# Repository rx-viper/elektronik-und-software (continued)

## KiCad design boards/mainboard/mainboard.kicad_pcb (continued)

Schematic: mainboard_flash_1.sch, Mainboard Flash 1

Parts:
C1101: 100n; C_0603
J1101: FL1_CS; Measurement_Point_Round-SMD-Pad_Small
J1102: FL1_SCK; Measurement_Point_Round-SMD-Pad_Small
J1103: FL1_MISO; Measurement_Point_Round-SMD-Pad_Small
J1104: FL1_MOSI; Measurement_Point_Round-SMD-Pad_Small
U1101: SST26VF064B; SOIJ-8_5.3x5.3mm_Pitch1.27mm

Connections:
+3V3: C1101.1, U1101.3 (WP), U1101.7 (HOLD), U1101.8 (VDD); also elsewhere on the board
/Mainboard microcontroller/Flash1_CS: J1101.1, U1101.1 (CE); also elsewhere on the board
/Mainboard microcontroller/Mainboard_Flash_1/MISO: J1103.1, U1101.2 (SO); also elsewhere on the board
/Mainboard microcontroller/Mainboard_Flash_1/MOSI: J1104.1, U1101.5 (SI); also elsewhere on the board
/Mainboard microcontroller/Mainboard_Flash_1/SCK: J1102.1, U1101.6 (SCK); also elsewhere on the board
GND: C1101.2, U1101.4 (Vss); also elsewhere on the board

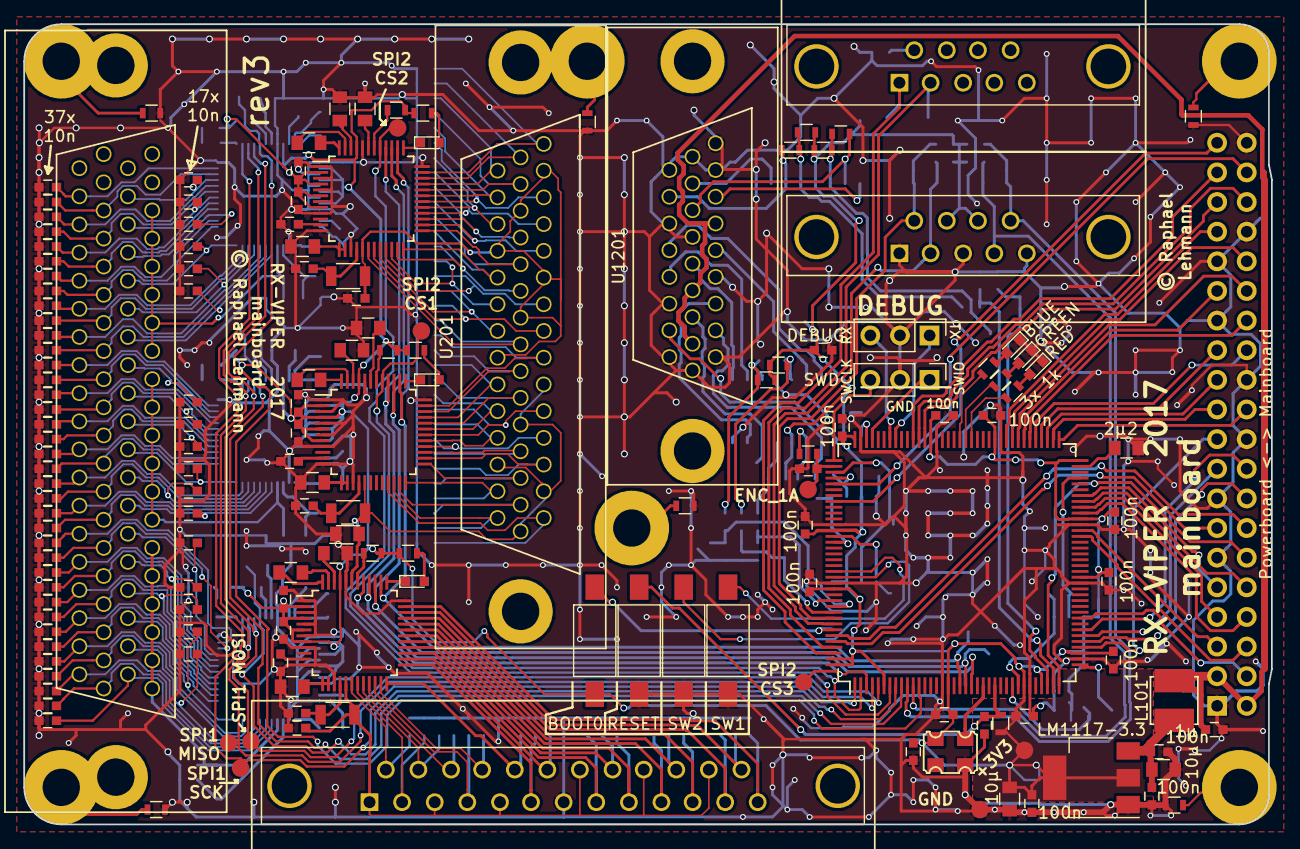
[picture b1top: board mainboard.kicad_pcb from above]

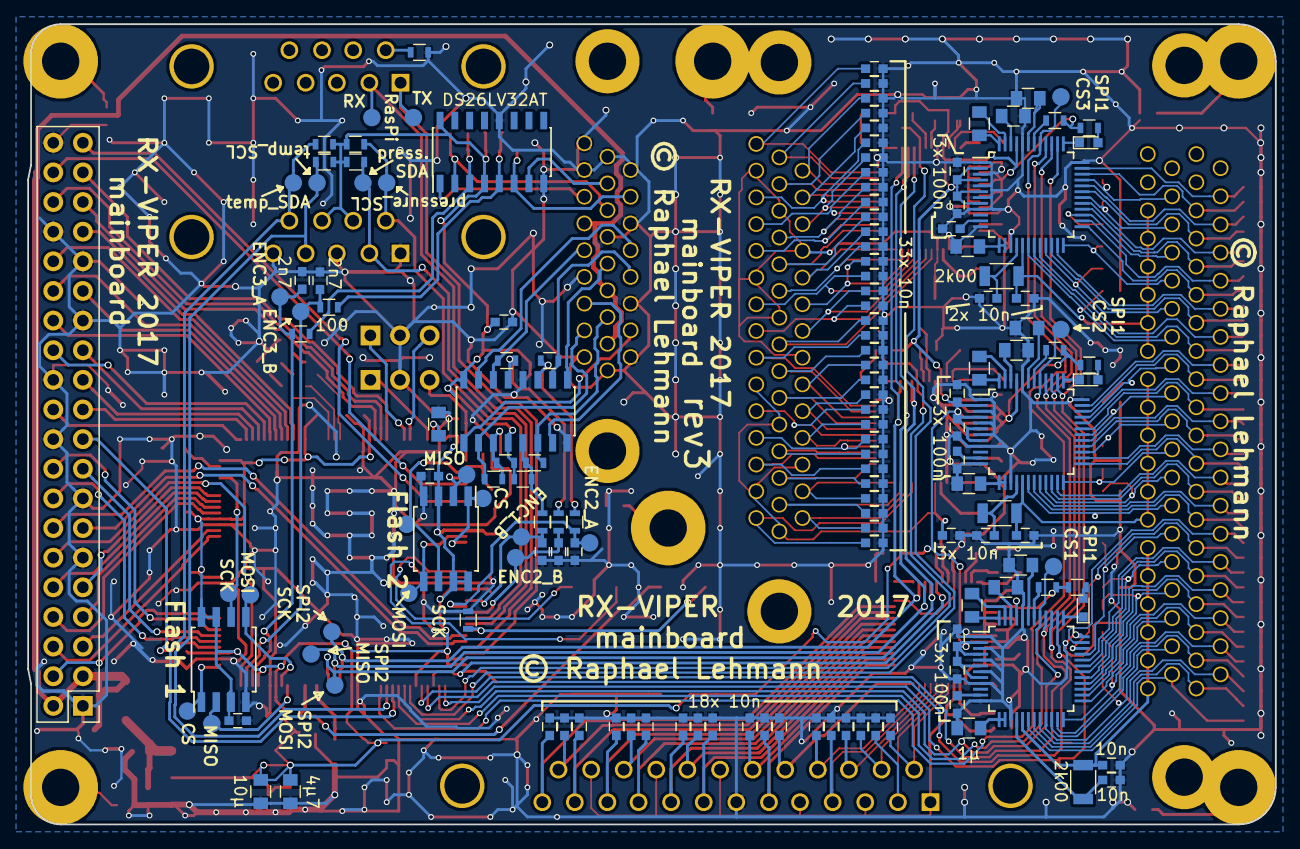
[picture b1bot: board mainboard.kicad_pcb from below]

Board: 2 copper layers, 106.9 x 68.6 mm, 319 parts (152 on the bottom side), 278 nets.

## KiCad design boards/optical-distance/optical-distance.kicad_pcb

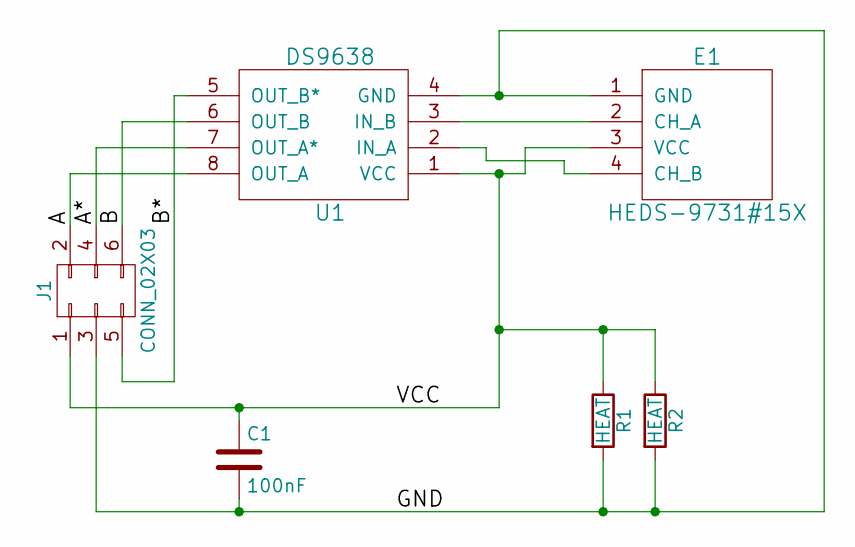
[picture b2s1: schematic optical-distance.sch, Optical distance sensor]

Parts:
C1: 100nF; C_0603_HandSoldering
E1: HEDS-9731#15X; HEDS-9731#X50
J1: CONN_02X03; Pin_Header_Straight_2x03_Pitch2.54mm
R1, R2: HEAT; R_1206
U1: DS9638; SOIC-8_3.9x4.9mm_Pitch1.27mm

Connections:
/A: J1.2, U1.8 (OUT_A)
/A*: J1.4, U1.7 (OUT_A*)
/B: J1.6, U1.6 (OUT_B)
/B*: J1.5, U1.5 (OUT_B*)
/GND: C1.2, E1.1 (GND), J1.3, R1.2, R2.2, U1.4 (GND)
/VCC: C1.1, E1.3 (VCC), J1.1, R1.1, R2.1, U1.1 (VCC)
unnamed: E1.2 (CH_A), U1.3 (IN_B)
unnamed: E1.4 (CH_B), U1.2 (IN_A)

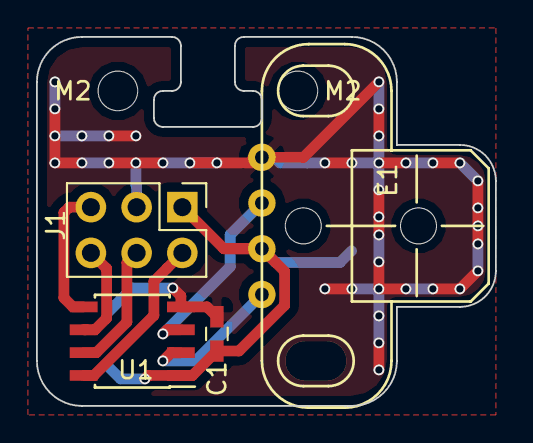
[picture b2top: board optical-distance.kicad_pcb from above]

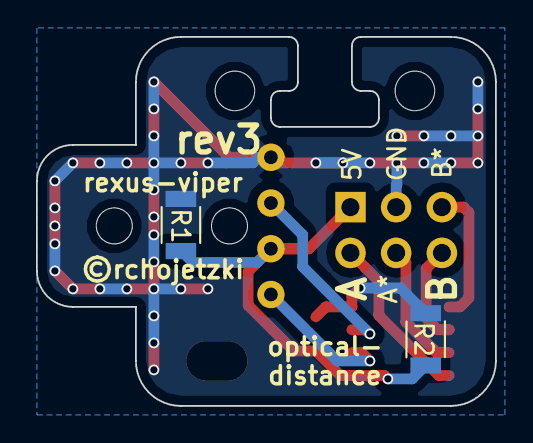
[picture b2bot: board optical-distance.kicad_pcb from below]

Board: 2 copper layers, 25.5 x 20.5 mm, 8 parts (2 on the bottom side), 8 nets.

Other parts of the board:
M2, M2#2: MountingHole_2.2mm_M2

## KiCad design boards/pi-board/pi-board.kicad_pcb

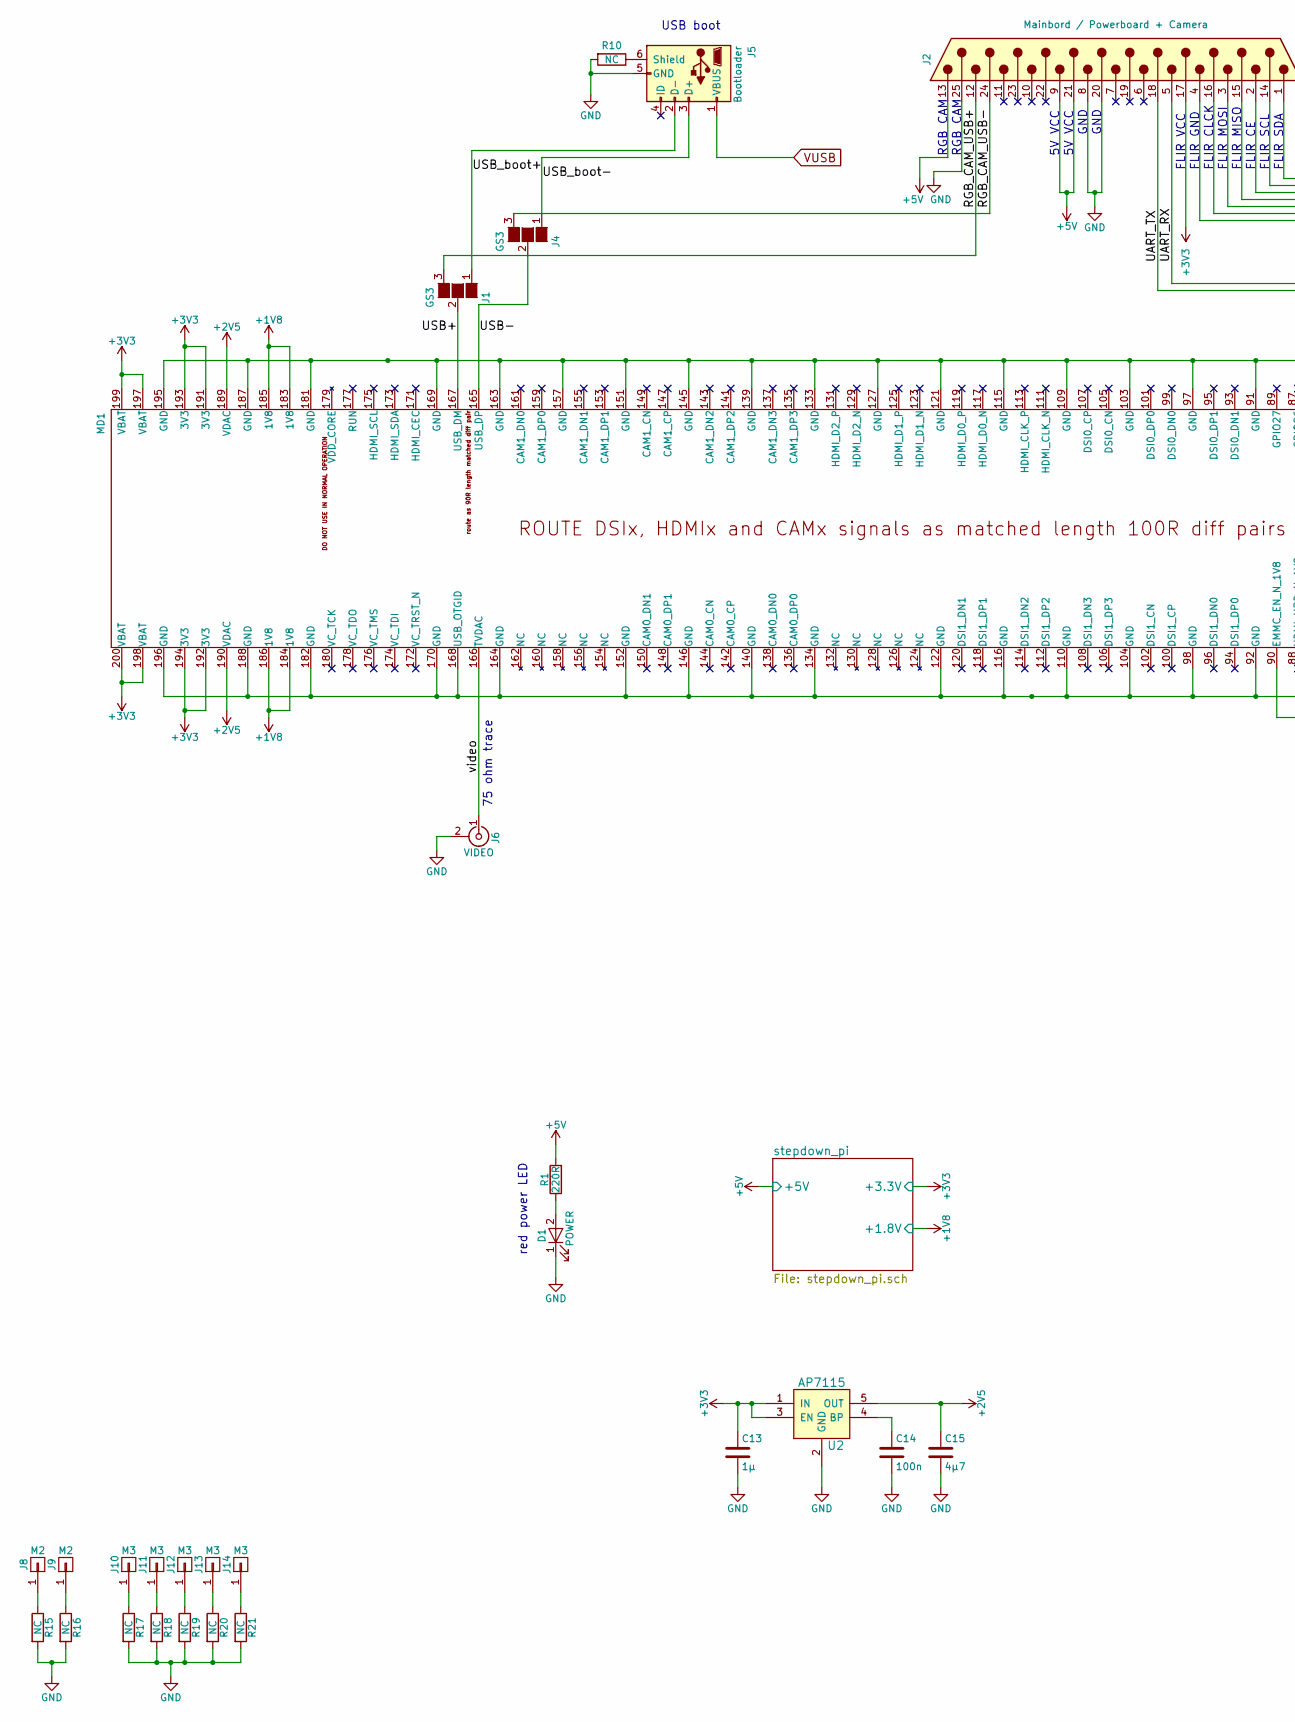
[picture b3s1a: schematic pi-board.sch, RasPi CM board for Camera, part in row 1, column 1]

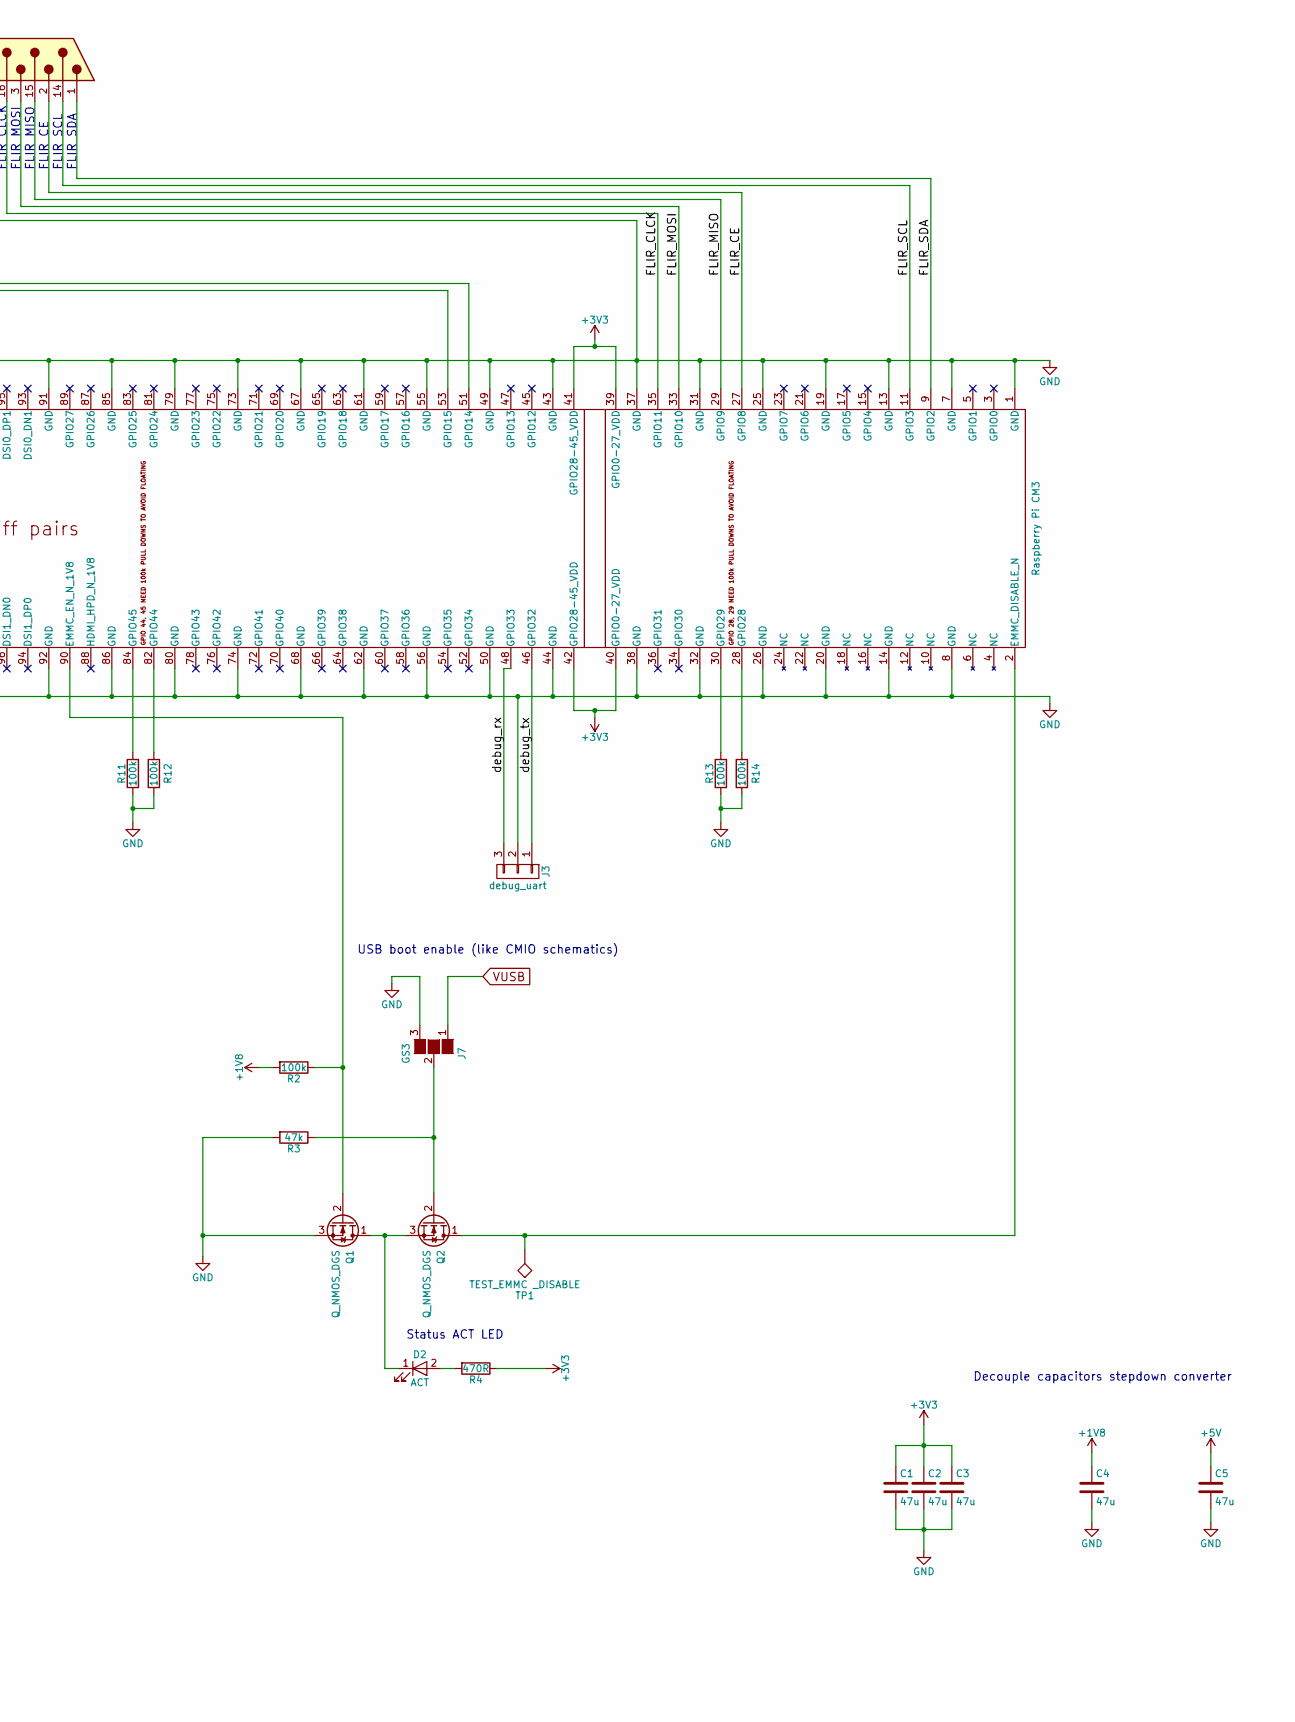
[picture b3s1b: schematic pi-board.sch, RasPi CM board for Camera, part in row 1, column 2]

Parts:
C1, C2, C3, C4, C5: 47u; C_0603_HandSoldering
C13: 1µ; C_0603
C14: 100n; C_0603
C15: 4µ7; C_0603
D1: POWER; LED_0603
D2: ACT; LED_0603
J1, J4, J7: GS3
J2: Mainbord / Powerboard + Camera; DB25MD
J3: debug_uart; Pin_Header_Straight_1x03_Pitch2.54mm
J5: Bootloader; USB_Micro-B
J6: VIDEO; BNC_Multi
J8, J9: M2; MountingHole_2.2mm_M2_Pad
J10, J11, J12, J13, J14: M3; MountingHole_3.2mm_M3_Pad
MD1: Raspberry Pi CM3; Socket_SODIMM_DDR1-2_TE_1612618_Debug
Q1, Q2: Q_NMOS_DGS; SOT-23
R1: 220R; R_0603_HandSoldering
R2, R13, R14: 100k; R_0603
R3: 47k; R_0603
R4: 470R; R_0603
R10, R15, R16, R17, R18, R19, R20, R21: NC; R_0603_HandSoldering
R11, R12: 100k; R_0603_HandSoldering
TP1: TEST_EMMC _DISABLE; Measurement_Point_Round-SMD-Pad_Small
U2: AP7115; SOT-353_SC-70-5_Handsoldering

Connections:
+1V8: C4.1, MD1.183 (1V8), MD1.184 (1V8), MD1.185 (1V8), MD1.186 (1V8), R2.2; also elsewhere on the board
+2V5: C15.1, MD1.189 (VDAC), MD1.190 (VDAC), U2.5 (OUT)
+3V3: C1.1, C2.1, C3.1, C13.1, J2.17, MD1.39 (GPIO0-27_VDD), MD1.40 (GPIO0-27_VDD), MD1.41 (GPIO28-45_VDD), MD1.42 (GPIO28-45_VDD), MD1.191 (3V3), MD1.192 (3V3), MD1.193 (3V3), MD1.194 (3V3), MD1.197 (VBAT), MD1.198 (VBAT), MD1.199 (VBAT), MD1.200 (VBAT), R4.1, U2.1 (IN), U2.3 (EN); also elsewhere on the board
+5V: C5.1, J2.9, J2.13, J2.21, R1.2; also elsewhere on the board
/FLIR_CE: J2.2, MD1.27 (GPIO8)
/FLIR_CLCK: J2.16, MD1.35 (GPIO11)
/FLIR_MISO: J2.15, MD1.29 (GPIO9)
/FLIR_MOSI: J2.3, MD1.33 (GPIO10)
/FLIR_SCL: J2.14, MD1.11 (GPIO3)
/FLIR_SDA: J2.1, MD1.9 (GPIO2)
/RGB_CAM_USB+: J1.3 (G3), J2.12
/RGB_CAM_USB-: J2.24, J4.3 (G3)
/UART_RX: J2.5, MD1.51 (GPIO14)
/UART_TX: J2.18, MD1.53 (GPIO15)
/USB+: J1.2 (G2), MD1.167 (USB_DM)
/USB-: J4.2 (G2), MD1.165 (USB_DP)
/USB_boot+: J1.1 (G1), J5.2 (D-)
/USB_boot-: J4.1 (G1), J5.3 (D+)
/debug_rx: J3.3, MD1.48 (GPIO33)
/debug_tx: J3.1, MD1.46 (GPIO32)
/video: J6.1 (In), MD1.166 (TVDAC)
GND: C1.2, C2.2, C3.2, C4.2, C5.2, C13.2, C14.2, C15.2, D1.1 (K), J2.4, J2.8, J2.20, J2.25, J3.2, J5.5 (GND), J6.2 (Ext), J7.3 (G3), MD1.1 (GND), MD1.7 (GND), MD1.8 (GND), MD1.13 (GND), MD1.14 (GND), MD1.19 (GND), MD1.20 (GND), MD1.25 (GND), MD1.26 (GND), MD1.31 (GND), MD1.32 (GND), MD1.37 (GND), MD1.38 (GND), MD1.43 (GND), MD1.44 (GND), MD1.49 (GND), MD1.50 (GND), MD1.55 (GND), MD1.56 (GND), MD1.61 (GND), MD1.62 (GND), MD1.67 (GND), MD1.68 (GND), MD1.73 (GND), MD1.74 (GND), MD1.79 (GND), MD1.80 (GND), MD1.85 (GND), MD1.86 (GND), MD1.91 (GND), MD1.92 (GND), MD1.97 (GND), MD1.98 (GND), MD1.103 (GND), MD1.104 (GND), MD1.109 (GND), MD1.110 (GND), MD1.115 (GND), MD1.116 (GND), MD1.121 (GND), MD1.122 (GND), MD1.127 (GND), MD1.133 (GND), MD1.134 (GND), MD1.139 (GND), MD1.140 (GND), MD1.145 (GND), MD1.146 (GND), MD1.151 (GND), MD1.152 (GND), MD1.157 (GND), MD1.163 (GND), MD1.164 (GND), MD1.168 (USB_OTGID), MD1.169 (GND), MD1.170 (GND), MD1.181 (GND), MD1.182 (GND), MD1.187 (GND), MD1.188 (GND), MD1.195 (GND), MD1.196 (GND), Q1.3 (S), R3.2, R10.2, R11.1, R12.1, R13.1, R14.1, R15.2, R16.2, R17.2, R18.2, R19.2, R20.2, R21.2, U2.2 (GND); also elsewhere on the board
unnamed: C14.1, U2.4 (BP)
unnamed: D1.2 (A), R1.1
unnamed: D2.1 (K), Q1.1 (D), Q2.3 (S)
unnamed: D2.2 (A), R4.2
unnamed: J5.6 (Shield), R10.1
unnamed: J7.2 (G2), Q2.2 (G), R3.1
unnamed: J8.1, R15.1
unnamed: J9.1, R16.1
unnamed: J10.1, R17.1
unnamed: J11.1, R18.1
unnamed: J12.1, R19.1
unnamed: J13.1, R20.1
unnamed: J14.1, R21.1
unnamed: MD1.2 (EMMC_DISABLE_N), Q2.1 (D), TP1.1
unnamed: MD1.28 (GPIO28), R14.2
unnamed: MD1.30 (GPIO29), R13.2
unnamed: MD1.82 (GPIO44), R12.2
unnamed: MD1.84 (GPIO45), R11.2
unnamed: MD1.90 (EMMC_EN_N_1V8), Q1.2 (G), R2.1
VUSB: J5.1 (VBUS), J7.1 (G1)

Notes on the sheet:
red power LED
Status ACT LED
USB boot enable (like CMIO schematics)
USB boot
RGB CAM
FLIR VCC
FLIR GND
FLIR CLCK
FLIR MOSI
FLIR MISO
FLIR CE
FLIR SCL
FLIR SDA
5V VCC
GND
Decouple capacitors stepdown converter
75 ohm trace

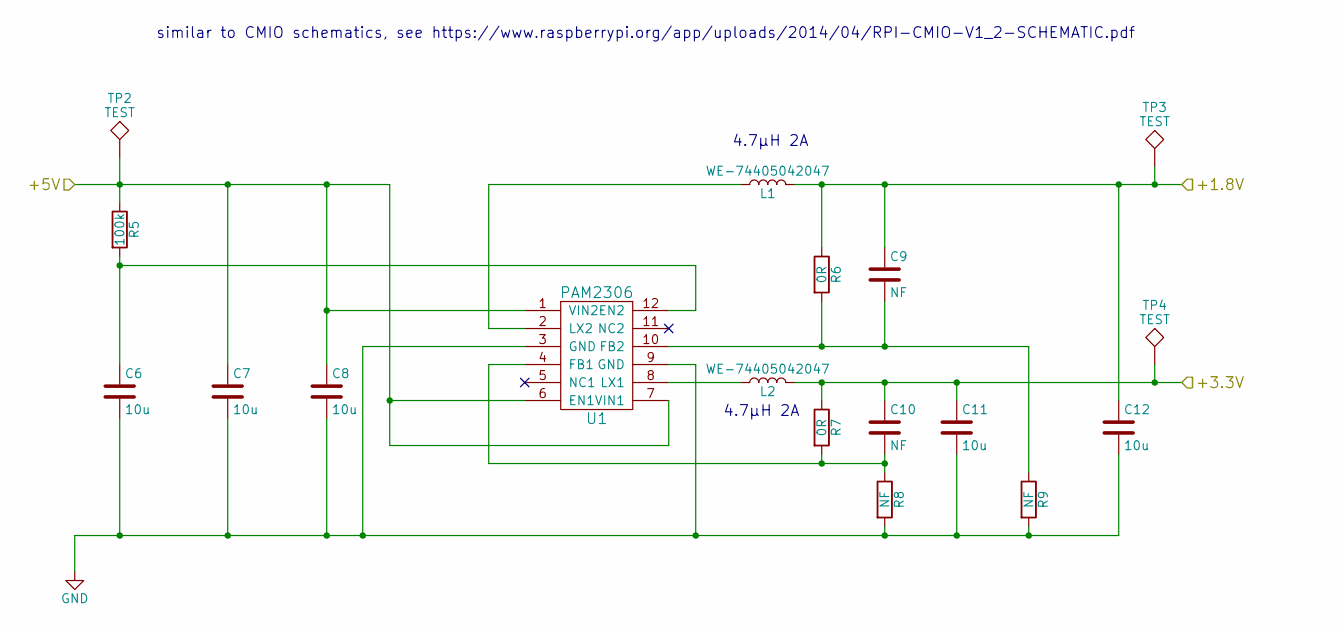
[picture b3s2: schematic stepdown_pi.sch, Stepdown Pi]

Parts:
C6, C8: 10u; C_0603
C7, C11, C12: 10u; C_0603_HandSoldering
C9, C10: NF; C_0603_HandSoldering
L1, L2: WE-74405042047; Inductor_Taiyo-Yuden_NR-50xx_HandSoldering
R5: 100k; R_0603
R6, R7: 0R; R_0603_HandSoldering
R8: NF; R_0603_HandSoldering
R9: NF; R_0603
TP2, TP3, TP4: TEST; Measurement_Point_Round-SMD-Pad_Small
U1: PAM2306; pam2306

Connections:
+1V8: C9.1, C12.1, L1.2, R6.1, TP3.1; also elsewhere on the board
+3V3: C10.1, C11.1, L2.2, R7.1, TP4.1; also elsewhere on the board
+5V: C7.1, C8.1, R5.1, TP2.1, U1.1 (VIN2), U1.6 (EN1), U1.7 (VIN1); also elsewhere on the board
GND: C6.2, C7.2, C8.2, C11.2, C12.2, R8.2, R9.2, U1.3 (GND), U1.9 (GND); also elsewhere on the board
unnamed: C6.1, R5.2, U1.12 (EN2)
unnamed: C9.2, R6.2, R9.1, U1.10 (FB2)
unnamed: C10.2, R7.2, R8.1, U1.4 (FB1)
unnamed: L1.1, U1.2 (LX2)
unnamed: L2.1, U1.8 (LX1)

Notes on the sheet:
similar to CMIO schematics, see https://www.raspberrypi.org/app/uploads/2014/04/RPI-CMIO-V1_2-SCHEMATIC.pdf
4.7µH 2A

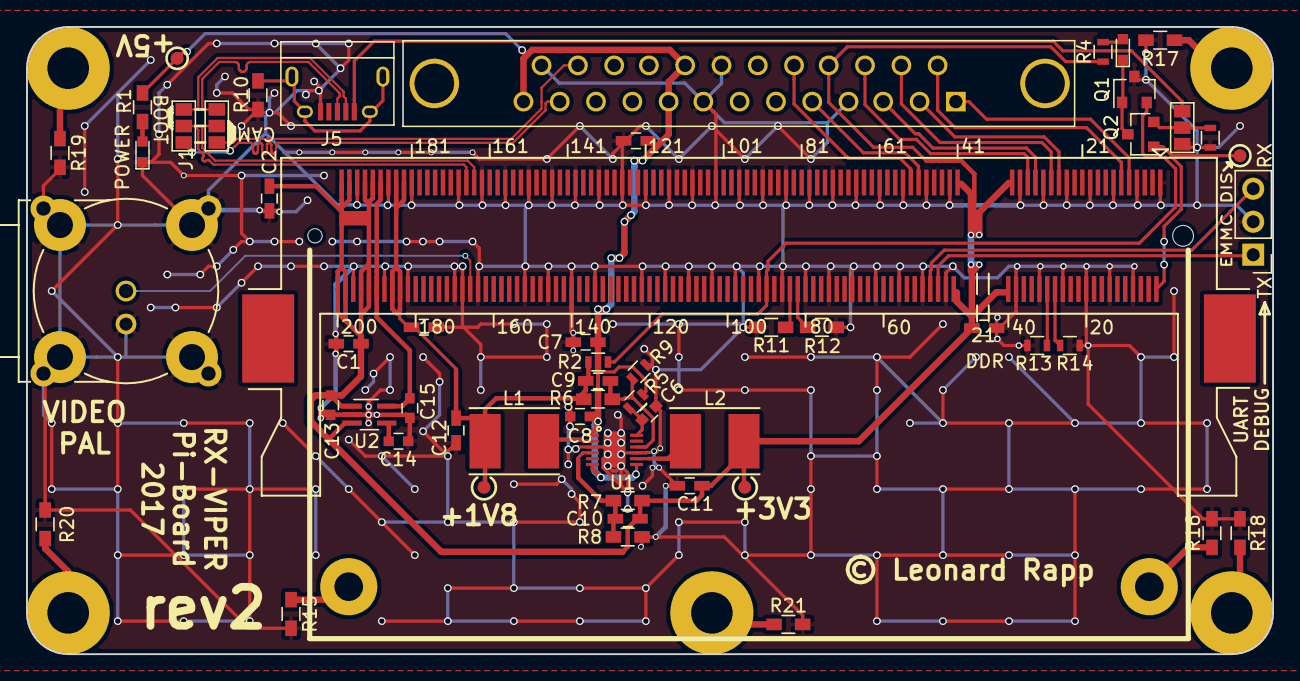
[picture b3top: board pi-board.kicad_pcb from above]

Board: 2 copper layers, 95.9 x 48.3 mm, 63 parts (0 on the bottom side), 47 nets.

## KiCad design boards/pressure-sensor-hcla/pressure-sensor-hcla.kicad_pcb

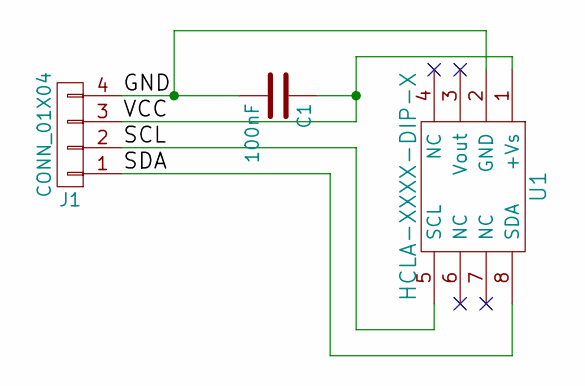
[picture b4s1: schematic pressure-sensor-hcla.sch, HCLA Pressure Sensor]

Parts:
C1: 100nF; C_0603_HandSoldering
J1: CONN_01X04; Pin_Header_Straight_1x04_Pitch2.54mm
U1: HCLA-XXXX-DIP-X; HCLA-DIP

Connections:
/GND: C1.2, J1.4, U1.2 (GND)
/SCL: J1.2, U1.5 (SCL)
/SDA: J1.1, U1.8 (SDA)
/VCC: C1.1, J1.3, U1.1 (+Vs)

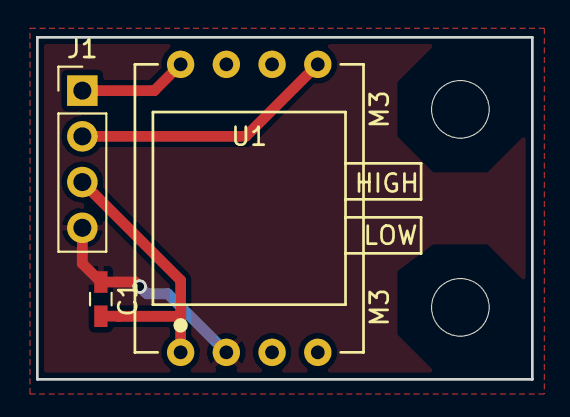
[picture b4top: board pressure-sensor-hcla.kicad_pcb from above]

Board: 2 copper layers, 27.5 x 19.0 mm, 5 parts (0 on the bottom side), 4 nets.

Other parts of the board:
M3, M3#2: MountingHole_3.2mm_M3

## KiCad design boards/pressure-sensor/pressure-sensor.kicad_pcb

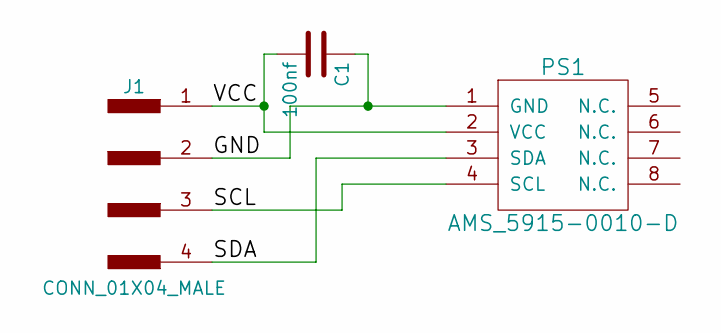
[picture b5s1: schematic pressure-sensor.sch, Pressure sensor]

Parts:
C1: 100nf; C_0603_HandSoldering
J1: CONN_01X04_MALE; Pin_Header_Straight_1x04_Pitch2.54mm
PS1: AMS_5915-0010-D; AMS_5915-XXXX-D_differential_pressure_sensor

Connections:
/GND: C1.1, J1.2, PS1.1 (GND)
/SCL: J1.3, PS1.4 (SCL)
/SDA: J1.4, PS1.3 (SDA)
/VCC: C1.2, J1.1, PS1.2 (VCC)

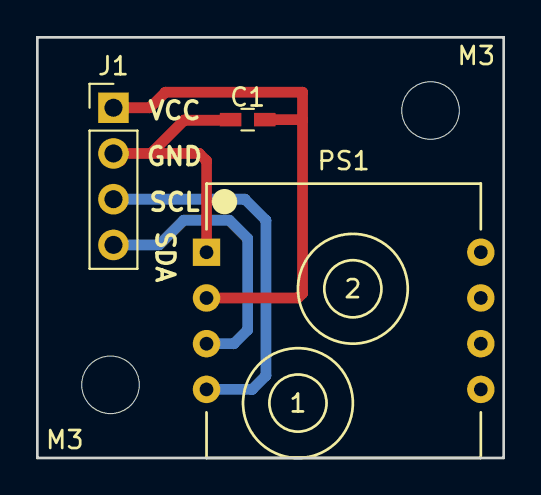
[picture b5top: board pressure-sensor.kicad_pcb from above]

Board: 2 copper layers, 25.9 x 23.4 mm, 5 parts (0 on the bottom side), 4 nets.

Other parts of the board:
M3, M3#2: MountingHole_3.2mm_M3

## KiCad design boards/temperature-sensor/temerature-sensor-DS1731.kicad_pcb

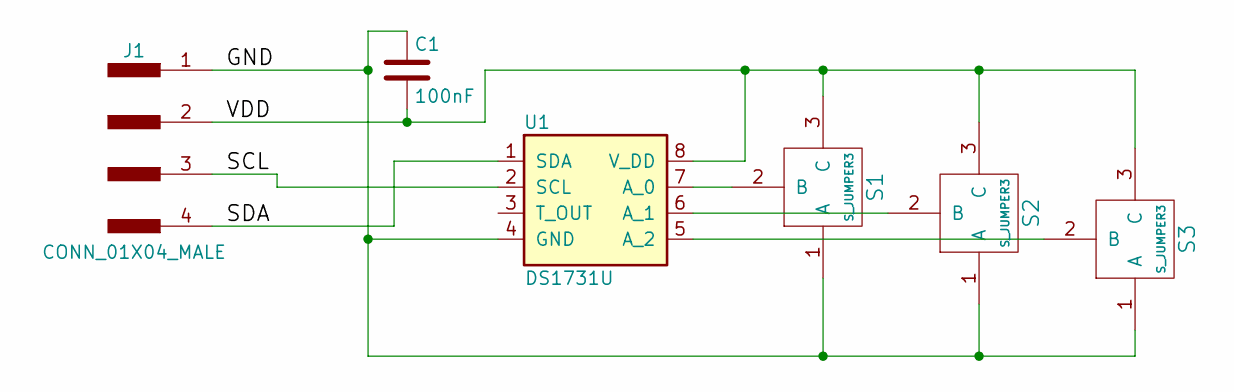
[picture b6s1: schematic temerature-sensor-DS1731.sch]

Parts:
C1: 100nF; C_0603_HandSoldering
J1: CONN_01X04_MALE; Pin_Header_Straight_1x04_Pitch2.54mm
S1, S2, S3: S_JUMPER3; S_JUMPER_3
U1: DS1731U; SOIC-8-1EP_3.9x4.9mm_Pitch1.27mm

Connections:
/GND: C1.1, J1.1, S1.1 (A), S2.1 (A), S3.1 (A), U1.4 (GND)
/SCL: J1.3, U1.2 (SCL)
/SDA: J1.4, U1.1 (SDA)
/VDD: C1.2, J1.2, S1.3 (C), S2.3 (C), S3.3 (C), U1.8 (V_DD)
unnamed: S1.2 (B), U1.7 (A_0)
unnamed: S2.2 (B), U1.6 (A_1)
unnamed: S3.2 (B), U1.5 (A_2)

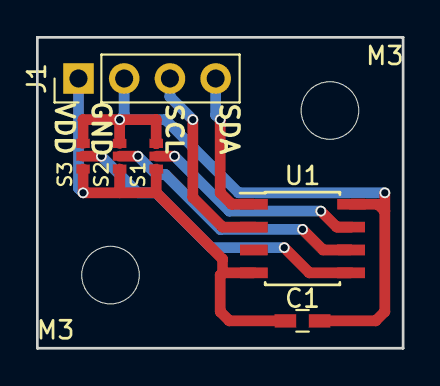
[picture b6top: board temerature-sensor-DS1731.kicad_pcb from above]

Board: 2 copper layers, 20.3 x 17.3 mm, 8 parts (0 on the bottom side), 7 nets.

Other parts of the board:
M3, M3#2: MountingHole_3.2mm_M3
